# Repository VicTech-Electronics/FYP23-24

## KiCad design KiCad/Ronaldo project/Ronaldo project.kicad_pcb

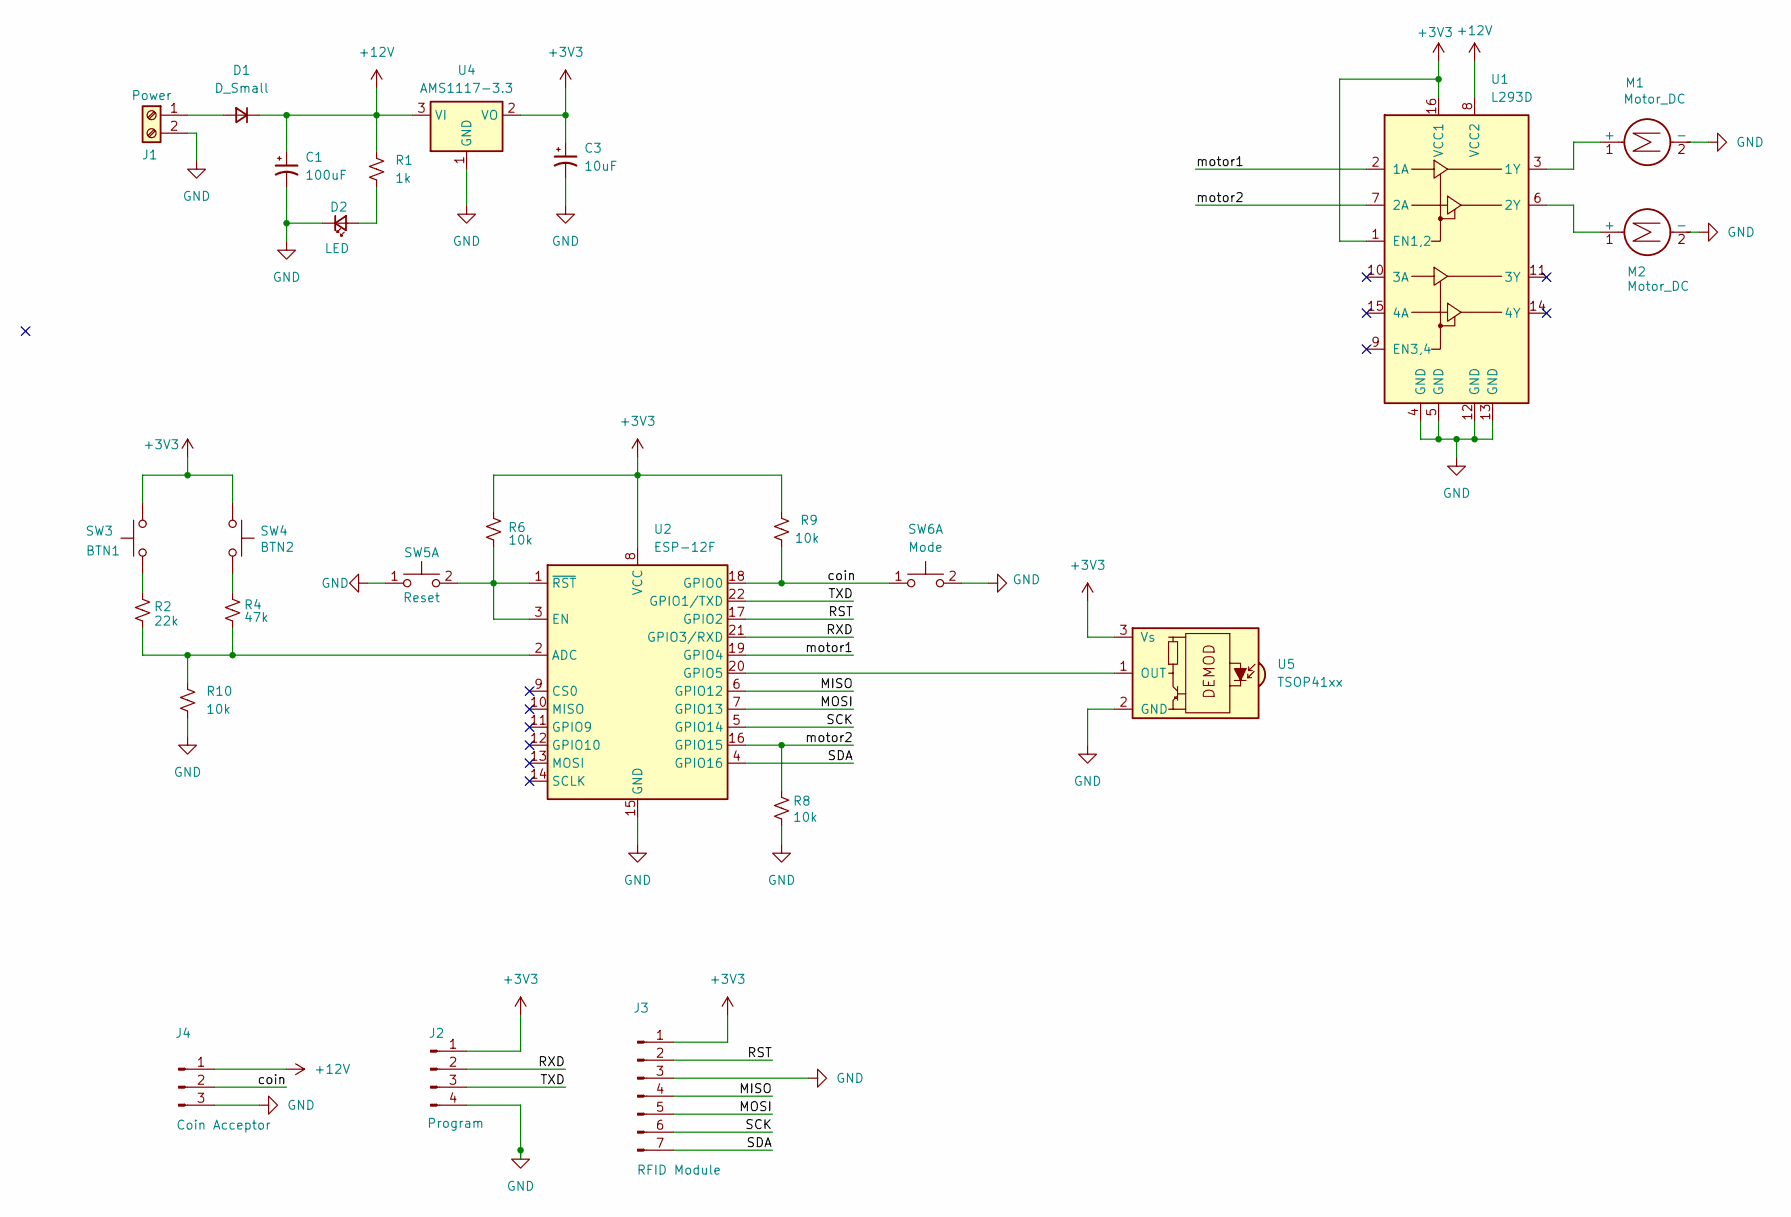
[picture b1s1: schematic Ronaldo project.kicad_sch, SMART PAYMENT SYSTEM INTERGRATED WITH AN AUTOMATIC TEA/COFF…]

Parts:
C1: 100uF; CP_Radial_D5.0mm_P2.50mm
C3: 10uF; CP_Radial_D5.0mm_P2.50mm
D1: D_Small; D_A-405_P10.16mm_Horizontal
D2: LED; LED_D3.0mm
J1: Power; TerminalBlock_bornier-2_P5.08mm
J2: Program; PinHeader_1x04_P2.54mm_Vertical
J3: RFID Module; PinHeader_1x07_P2.54mm_Vertical
J4: Coin Acceptor; PinHeader_1x03_P2.54mm_Vertical
M1, M2: Motor_DC; TerminalBlock_bornier-2_P5.08mm
R1: 1k; R_Axial_DIN0207_L6.3mm_D2.5mm_P10.16mm_Horizontal
R2: 22k; R_Axial_DIN0207_L6.3mm_D2.5mm_P10.16mm_Horizontal
R4: 47k; R_Axial_DIN0207_L6.3mm_D2.5mm_P10.16mm_Horizontal
R6, R8, R9, R10: 10k; R_Axial_DIN0207_L6.3mm_D2.5mm_P10.16mm_Horizontal
SW3: BTN1; TestPoint_2Pads_Pitch2.54mm_Drill0.8mm
SW4: BTN2; TestPoint_2Pads_Pitch2.54mm_Drill0.8mm
SW5: Reset; SW_PUSH_6mm
SW6: Mode; SW_PUSH_6mm
U1: L293D; DIP-16_W7.62mm
U2: ESP-12F; ESP-12E
U4: AMS1117-3.3; SOT-223-3_TabPin2
U5: TSOP41xx; Vishay_MOLD-3Pin

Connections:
+3V3: C3.1, J2.1, J3.1, R6.2, R9.1, SW3.2, SW4.1, U1.1 (EN1,2), U1.16 (VCC1), U2.8 (VCC), U4.2 (VO), U5.3 (Vs)
+12V: C1.1, D1.1 (K), J4.1, R1.1, U1.8 (VCC2), U4.3 (VI)
/MISO: J3.4, U2.6 (GPIO12)
/MOSI: J3.5, U2.7 (GPIO13)
/RST: J3.2, U2.17 (GPIO2)
/RXD: J2.2, U2.21 (GPIO3/RXD)
/SCK: J3.6, U2.5 (GPIO14)
/SDA: J3.7, U2.4 (GPIO16)
/TXD: J2.3, U2.22 (GPIO1/TXD)
/coin: J4.2, R9.2, SW6.1 (C), U2.18 (GPIO0)
/motor1: U1.2 (1A), U2.19 (GPIO4)
/motor2: R8.1, U1.7 (2A), U2.16 (GPIO15)
GND: C1.2, C3.2, D2.1 (K), J1.2, J2.4, J3.3, J4.3, M1.2 (-), M2.2 (-), R8.2, R10.1, SW5.1 (C), SW6.2 (D), U1.4 (GND), U1.5 (GND), U1.12 (GND), U1.13 (GND), U2.15 (GND), U4.1 (GND), U5.2 (GND)
unnamed: D1.2 (A), J1.1
unnamed: D2.2 (A), R1.2
unnamed: M1.1 (+), U1.3 (1Y)
unnamed: M2.1 (+), U1.6 (2Y)
unnamed: R2.2, SW3.1
unnamed: R4.2, SW4.2
unnamed: R6.1, SW5.2 (D), U2.1 (~RST), U2.3 (EN)
unnamed: R2.1, R4.1, R10.2, U2.2 (ADC)
unnamed: U2.20 (GPIO5), U5.1 (OUT)

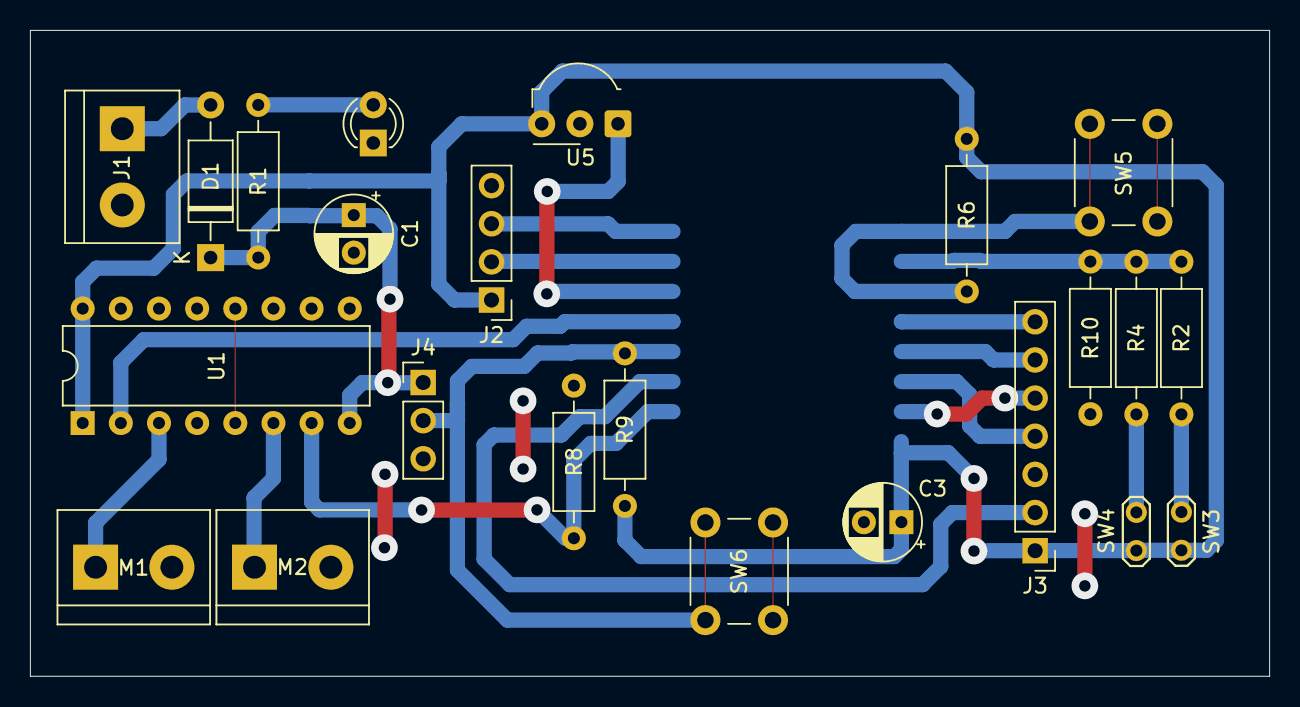
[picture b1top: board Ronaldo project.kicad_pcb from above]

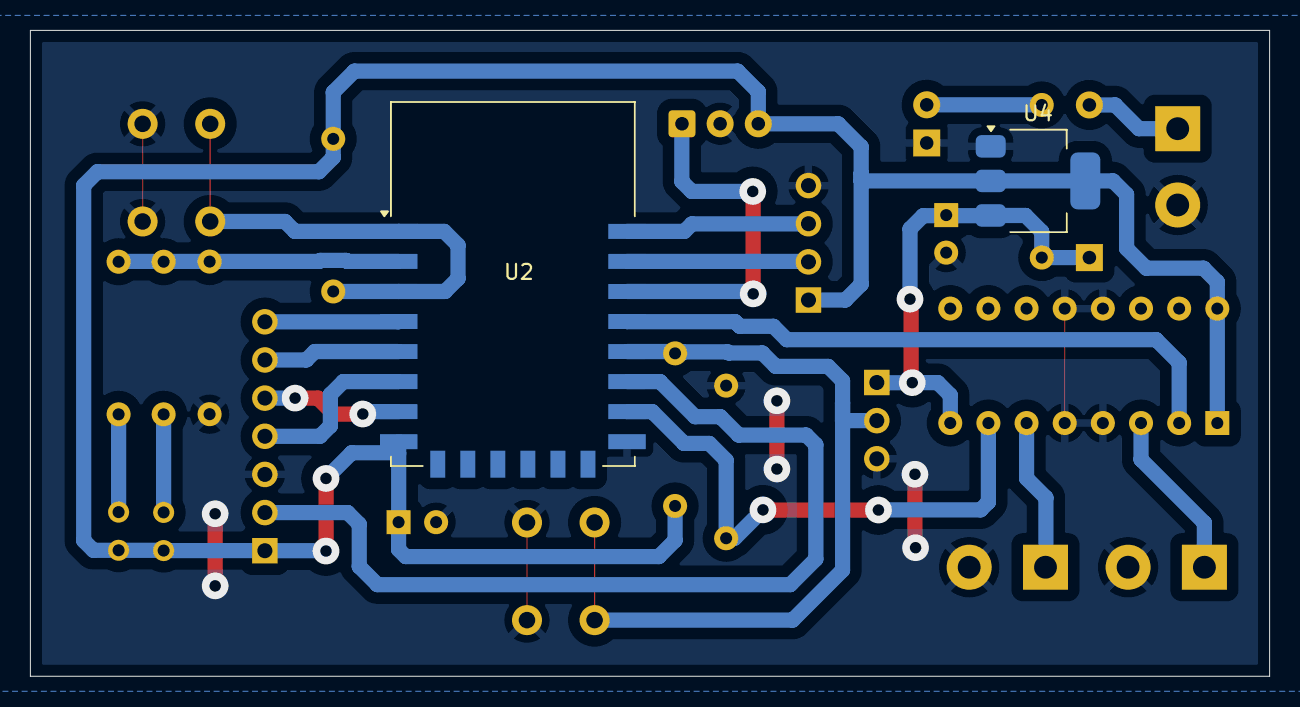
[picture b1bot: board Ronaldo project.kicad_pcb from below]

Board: 2 copper layers, 82.5 x 43.0 mm, 25 parts (2 on the bottom side), 22 nets.

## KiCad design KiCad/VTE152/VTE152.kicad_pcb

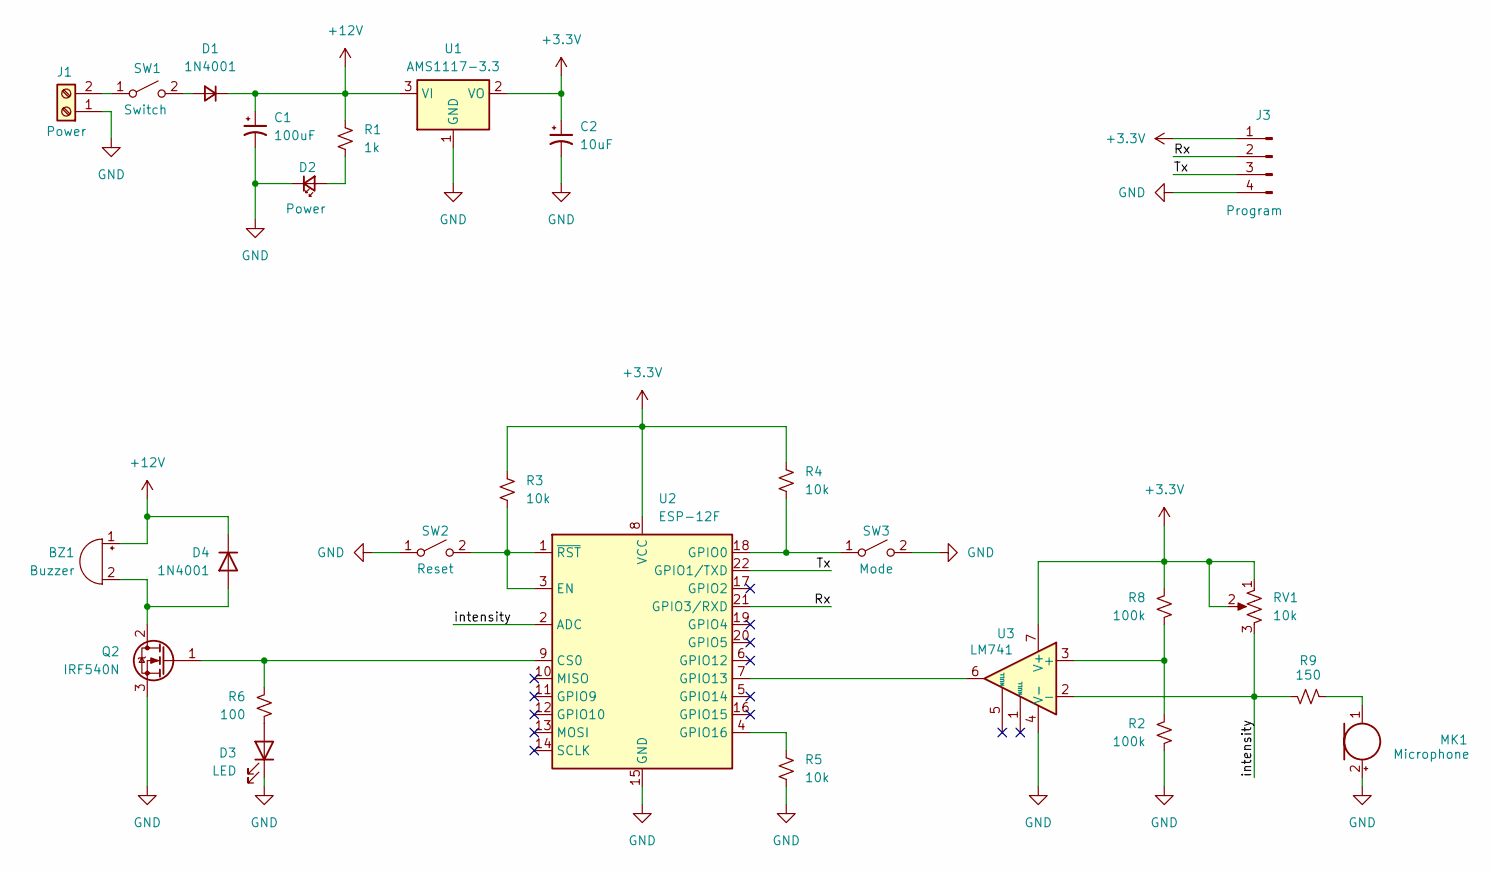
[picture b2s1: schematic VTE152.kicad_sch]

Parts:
BZ1: Buzzer; PinHeader_1x02_P2.54mm_Vertical
C1: 100uF; CP_Radial_D5.0mm_P2.50mm
C2: 10uF; CP_Radial_D5.0mm_P2.50mm
D1: 1N4001; D_A-405_P10.16mm_Horizontal
D2: Power; LED_D3.0mm
D3: LED; LED_D3.0mm
D4: 1N4001; D_DO-41_SOD81_P10.16mm_Horizontal
J1: Power; TerminalBlock_bornier-2_P5.08mm
J3: Program; PinHeader_1x04_P2.54mm_Vertical
MK1: Microphone; MagneticBuzzer_Kobitone_254-EMB73-RO
Q2: IRF540N; TO-220-3_Vertical
R1: 1k; R_Axial_DIN0207_L6.3mm_D2.5mm_P10.16mm_Horizontal
R2, R8: 100k; R_Axial_DIN0207_L6.3mm_D2.5mm_P10.16mm_Horizontal
R3, R4, R5: 10k; R_Axial_DIN0207_L6.3mm_D2.5mm_P10.16mm_Horizontal
R6: 100; R_Axial_DIN0207_L6.3mm_D2.5mm_P10.16mm_Horizontal
R9: 150; R_Axial_DIN0207_L6.3mm_D2.5mm_P10.16mm_Horizontal
RV1: 10k; Potentiometer_Runtron_RM-065_Vertical
SW1: Switch; TestPoint_2Pads_Pitch2.54mm_Drill0.8mm
SW2: Reset; SW_PUSH_6mm
SW3: Mode; SW_PUSH_6mm
U1: AMS1117-3.3; SOT-223-3_TabPin2
U2: ESP-12F; ESP-12E
U3: LM741; DIP-8_W7.62mm_LongPads

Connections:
+3.3V: C2.1, J3.1, R3.1, R4.1, R8.2, RV1.1, RV1.2, U1.2 (VO), U2.8 (VCC), U3.7 (V+)
+12V: BZ1.1 (+), C1.1, D1.1 (K), D4.1 (K), R1.1, U1.3 (VI)
/Rx: J3.2, U2.21 (GPIO3/RXD)
/Tx: J3.3, U2.22 (GPIO1/TXD)
/intensity: R9.1, RV1.3, U2.2 (ADC), U3.2 (-)
GND: C1.2, C2.2, D2.1 (K), D3.1 (K), J1.1, J3.4, MK1.2 (+), Q2.3 (S), R2.1, R5.2, SW2.1 (A), SW3.2 (B), U1.1 (GND), U2.15 (GND), U3.4 (V-)
unnamed: BZ1.2 (-), D4.2 (A), Q2.2 (D)
unnamed: D1.2 (A), SW1.2 (B)
unnamed: D2.2 (A), R1.2
unnamed: D3.2 (A), R6.2
unnamed: J1.2, SW1.1 (A)
unnamed: MK1.1 (-), R9.2
unnamed: Q2.1 (G), R6.1, U2.9 (CS0)
unnamed: R3.2, SW2.2 (B), U2.1 (~RST), U2.3 (EN)
unnamed: R4.2, SW3.1 (A), U2.18 (GPIO0)
unnamed: U2.7 (GPIO13), U3.6
unnamed: R5.1, U2.4 (GPIO16)
unnamed: R2.2, R8.1, U3.3 (+)

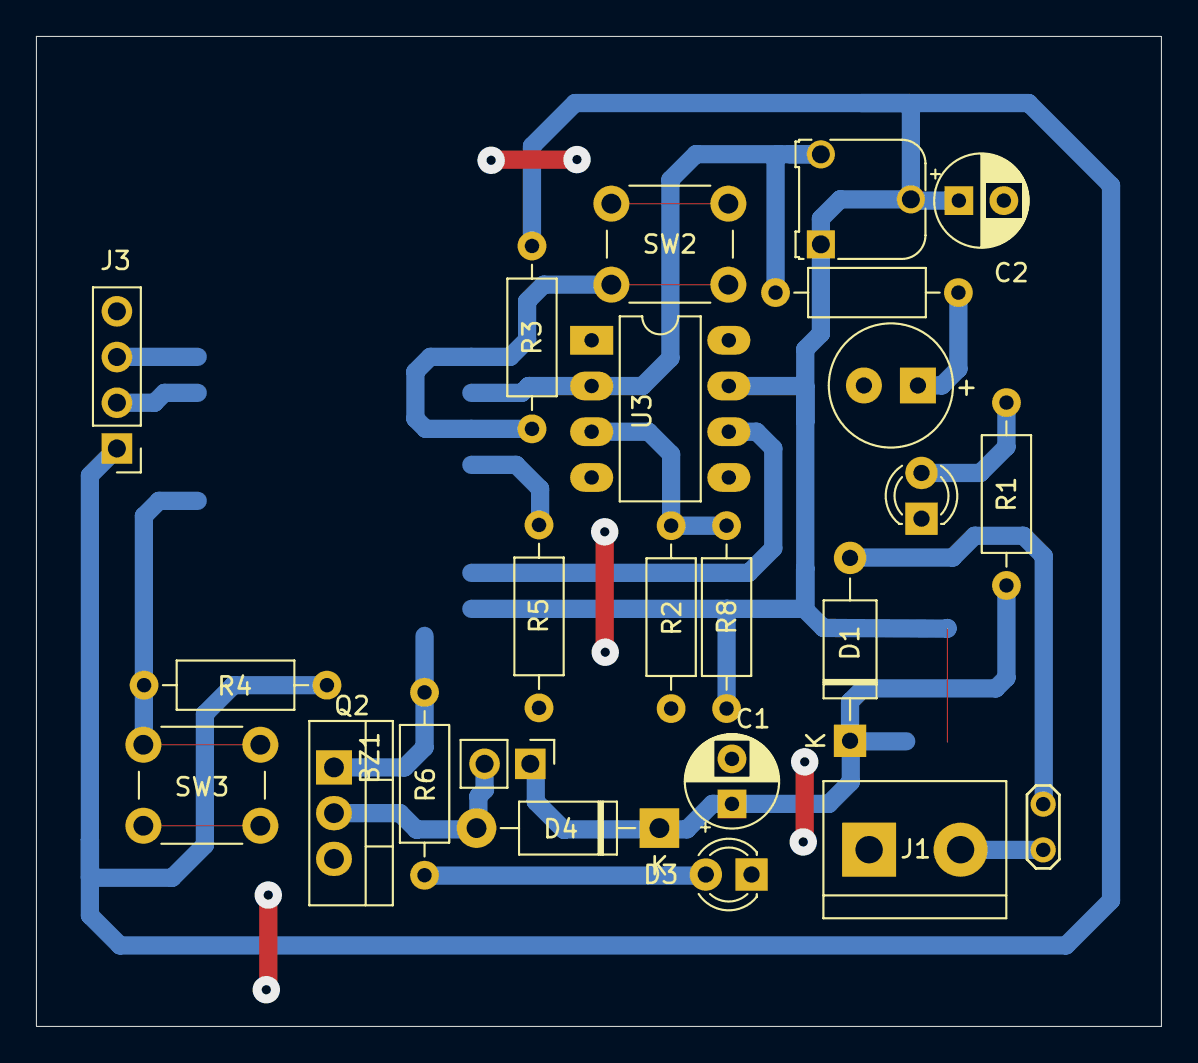
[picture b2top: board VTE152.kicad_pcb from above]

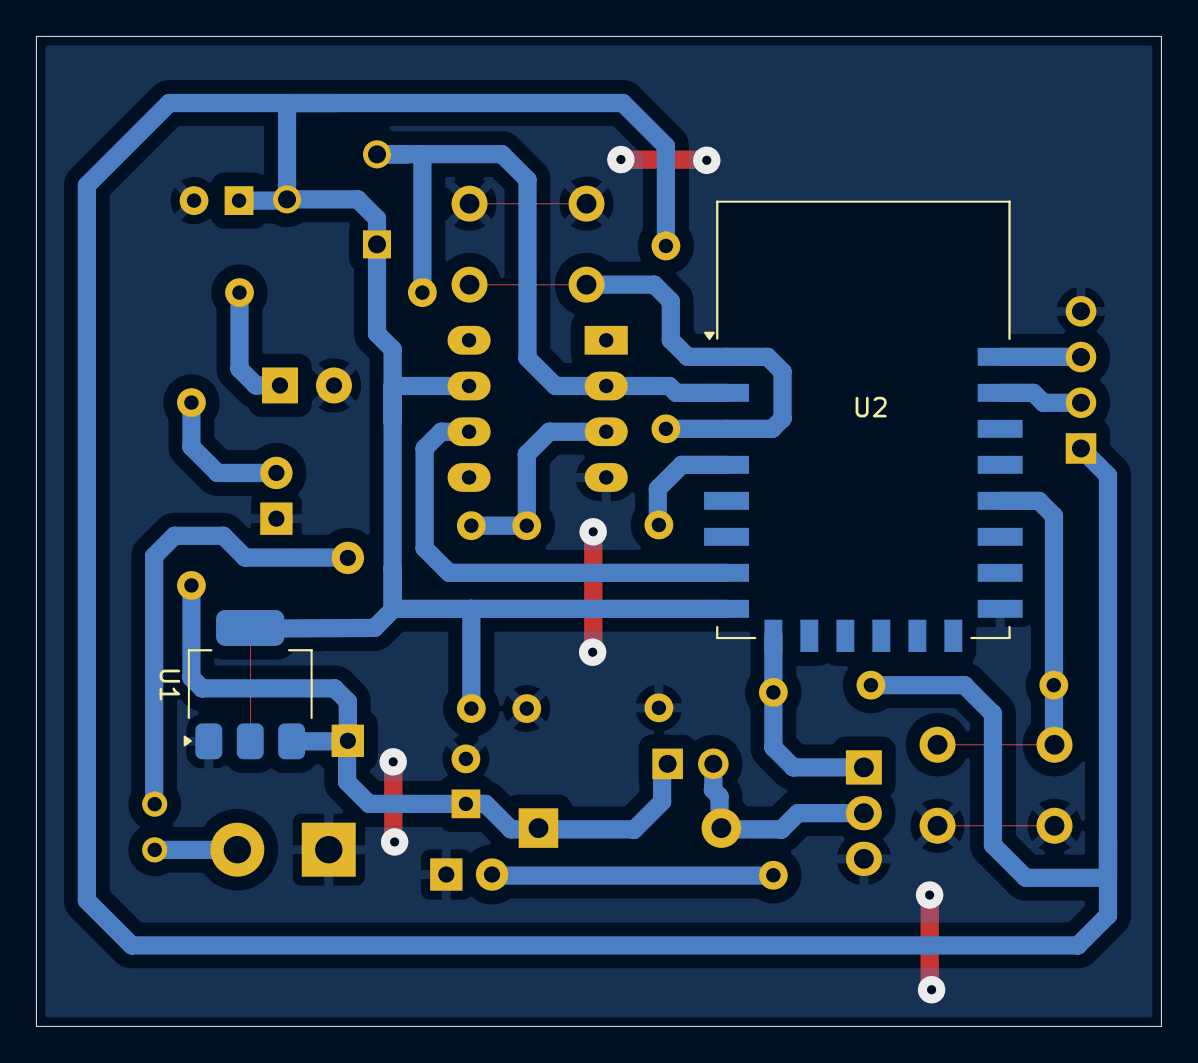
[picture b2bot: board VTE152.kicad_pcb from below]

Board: 2 copper layers, 62.5 x 55.0 mm, 26 parts (2 on the bottom side), 18 nets.

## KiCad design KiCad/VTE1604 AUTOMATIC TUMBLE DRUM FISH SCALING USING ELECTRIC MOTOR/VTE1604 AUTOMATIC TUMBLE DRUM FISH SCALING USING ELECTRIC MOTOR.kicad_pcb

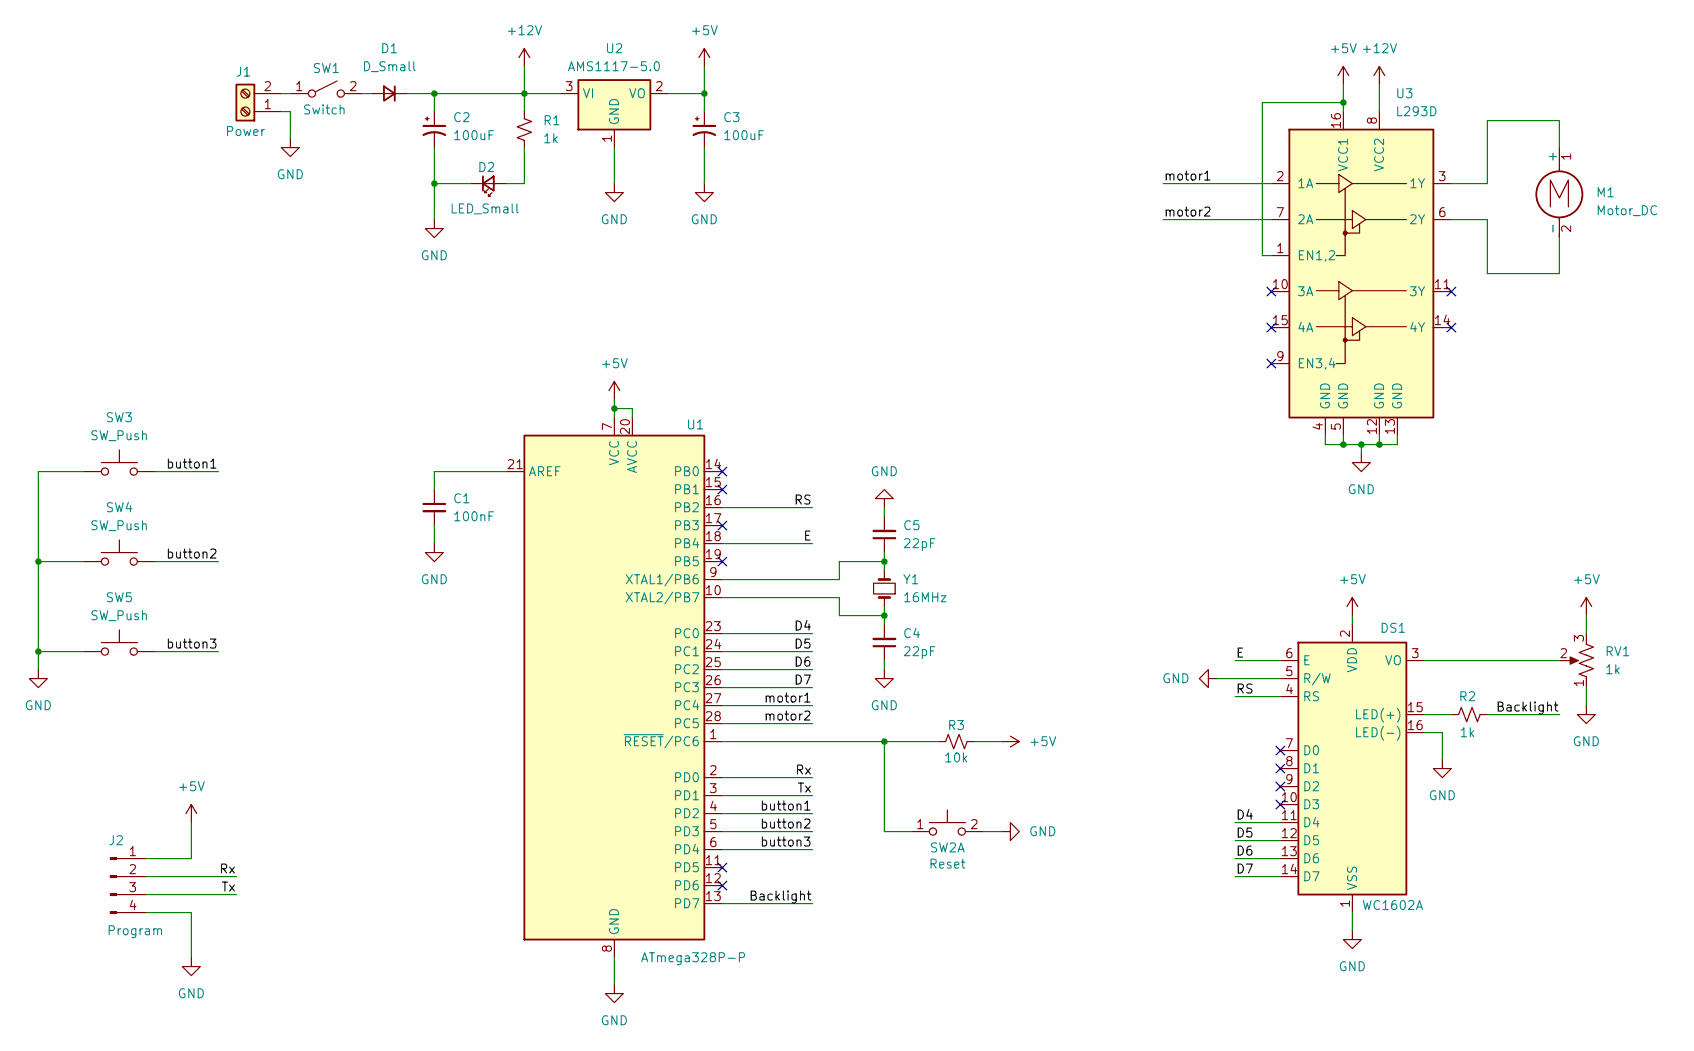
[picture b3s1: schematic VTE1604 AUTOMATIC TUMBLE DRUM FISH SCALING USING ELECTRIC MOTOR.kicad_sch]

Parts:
C1: 100nF; C_Disc_D3.0mm_W1.6mm_P2.50mm
C2, C3: 100uF; CP_Radial_D5.0mm_P2.50mm
C4, C5: 22pF; C_Disc_D3.0mm_W1.6mm_P2.50mm
D1: D_Small; D_A-405_P10.16mm_Horizontal
D2: LED_Small; LED_D3.0mm
DS1: WC1602A
J1: Power; TerminalBlock_bornier-2_P5.08mm
J2: Program; PinHeader_1x04_P2.54mm_Vertical
M1: Motor_DC; TerminalBlock_bornier-2_P5.08mm
R1, R2: 1k; R_Axial_DIN0207_L6.3mm_D2.5mm_P10.16mm_Horizontal
R3: 10k; R_Axial_DIN0207_L6.3mm_D2.5mm_P10.16mm_Horizontal
RV1: 1k; Potentiometer_Runtron_RM-065_Vertical
SW1: Switch; TestPoint_2Pads_Pitch2.54mm_Drill0.8mm
SW2: Reset; SW_PUSH_6mm
SW3, SW4, SW5: SW_Push; TestPoint_2Pads_Pitch2.54mm_Drill0.8mm
U1: ATmega328P-P; DIP-28_W7.62mm_Socket_LongPads
U2: AMS1117-5.0; SOT-223-3_TabPin2
U3: L293D; DIP-16_W7.62mm_Socket_LongPads
Y1: 16MHz; Crystal_HC50_Vertical

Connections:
+5V: C3.1, DS1.2 (VDD), J2.1, R3.2, RV1.3, U1.7 (VCC), U1.20 (AVCC), U2.2 (VO), U3.1 (EN1,2), U3.16 (VCC1)
+12V: C2.1, D1.1 (K), R1.1, U2.3 (VI), U3.8 (VCC2)
/Backlight: R2.2, U1.13 (PD7)
/D4: DS1.11 (D4), U1.23 (PC0)
/D5: DS1.12 (D5), U1.24 (PC1)
/D6: DS1.13 (D6), U1.25 (PC2)
/D7: DS1.14 (D7), U1.26 (PC3)
/E: DS1.6 (E), U1.18 (PB4)
/RS: DS1.4 (RS), U1.16 (PB2)
/Rx: J2.2, U1.2 (PD0)
/Tx: J2.3, U1.3 (PD1)
/button1: SW3.2, U1.4 (PD2)
/button2: SW4.2, U1.5 (PD3)
/button3: SW5.2, U1.6 (PD4)
/motor1: U1.27 (PC4), U3.2 (1A)
/motor2: U1.28 (PC5), U3.7 (2A)
GND: C1.2, C2.2, C3.2, C4.1, C5.2, D2.1 (K), DS1.1 (VSS), DS1.5 (R/W), DS1.16 (LED(-)), J1.1, J2.4, RV1.1, SW2.2 (D), SW3.1, SW4.1, SW5.1, U1.8 (GND), U1.22 (GND), U2.1 (GND), U3.4 (GND), U3.5 (GND), U3.12 (GND), U3.13 (GND)
unnamed: D1.2 (A), SW1.2 (B)
unnamed: D2.2 (A), R1.2
unnamed: DS1.15 (LED(+)), R2.1
unnamed: DS1.3 (VO), RV1.2
unnamed: J1.2, SW1.1 (A)
unnamed: M1.1 (+), U3.3 (1Y)
unnamed: M1.2 (-), U3.6 (2Y)
unnamed: R3.1, SW2.1 (C), U1.1 (~RESET/PC6)
unnamed: C1.1, U1.21 (AREF)
unnamed: C5.1, U1.9 (XTAL1/PB6), Y1.2
unnamed: C4.2, U1.10 (XTAL2/PB7), Y1.1

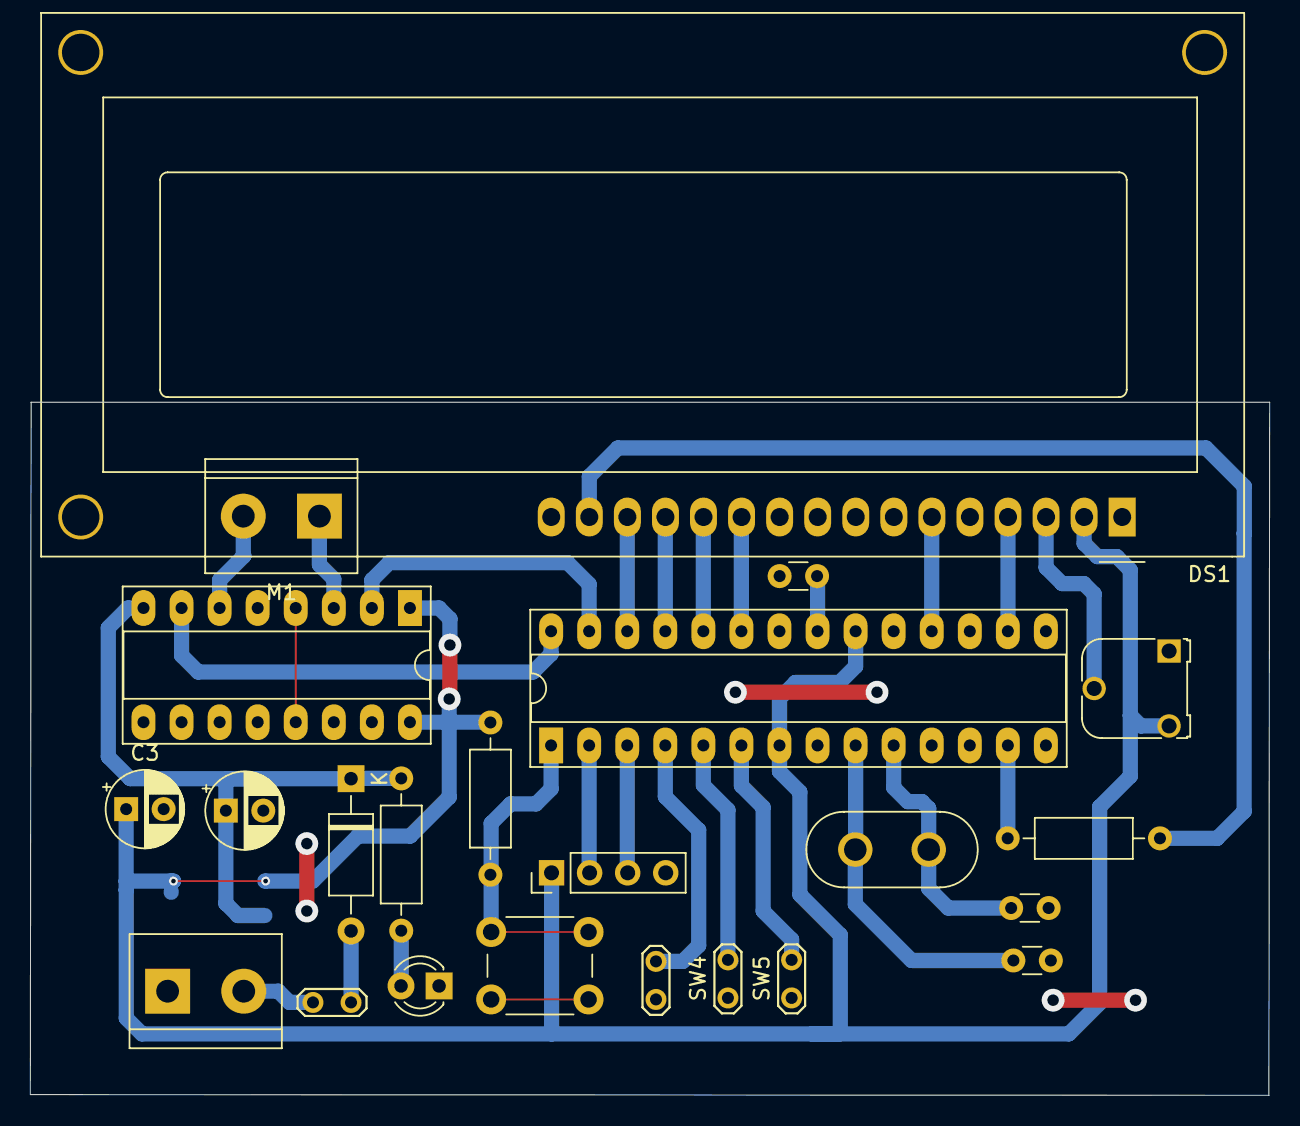
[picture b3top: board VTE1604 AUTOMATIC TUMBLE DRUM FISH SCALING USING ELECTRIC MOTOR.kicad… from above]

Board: 2 copper layers, 82.7 x 46.2 mm, 24 parts (1 on the bottom side), 28 nets.

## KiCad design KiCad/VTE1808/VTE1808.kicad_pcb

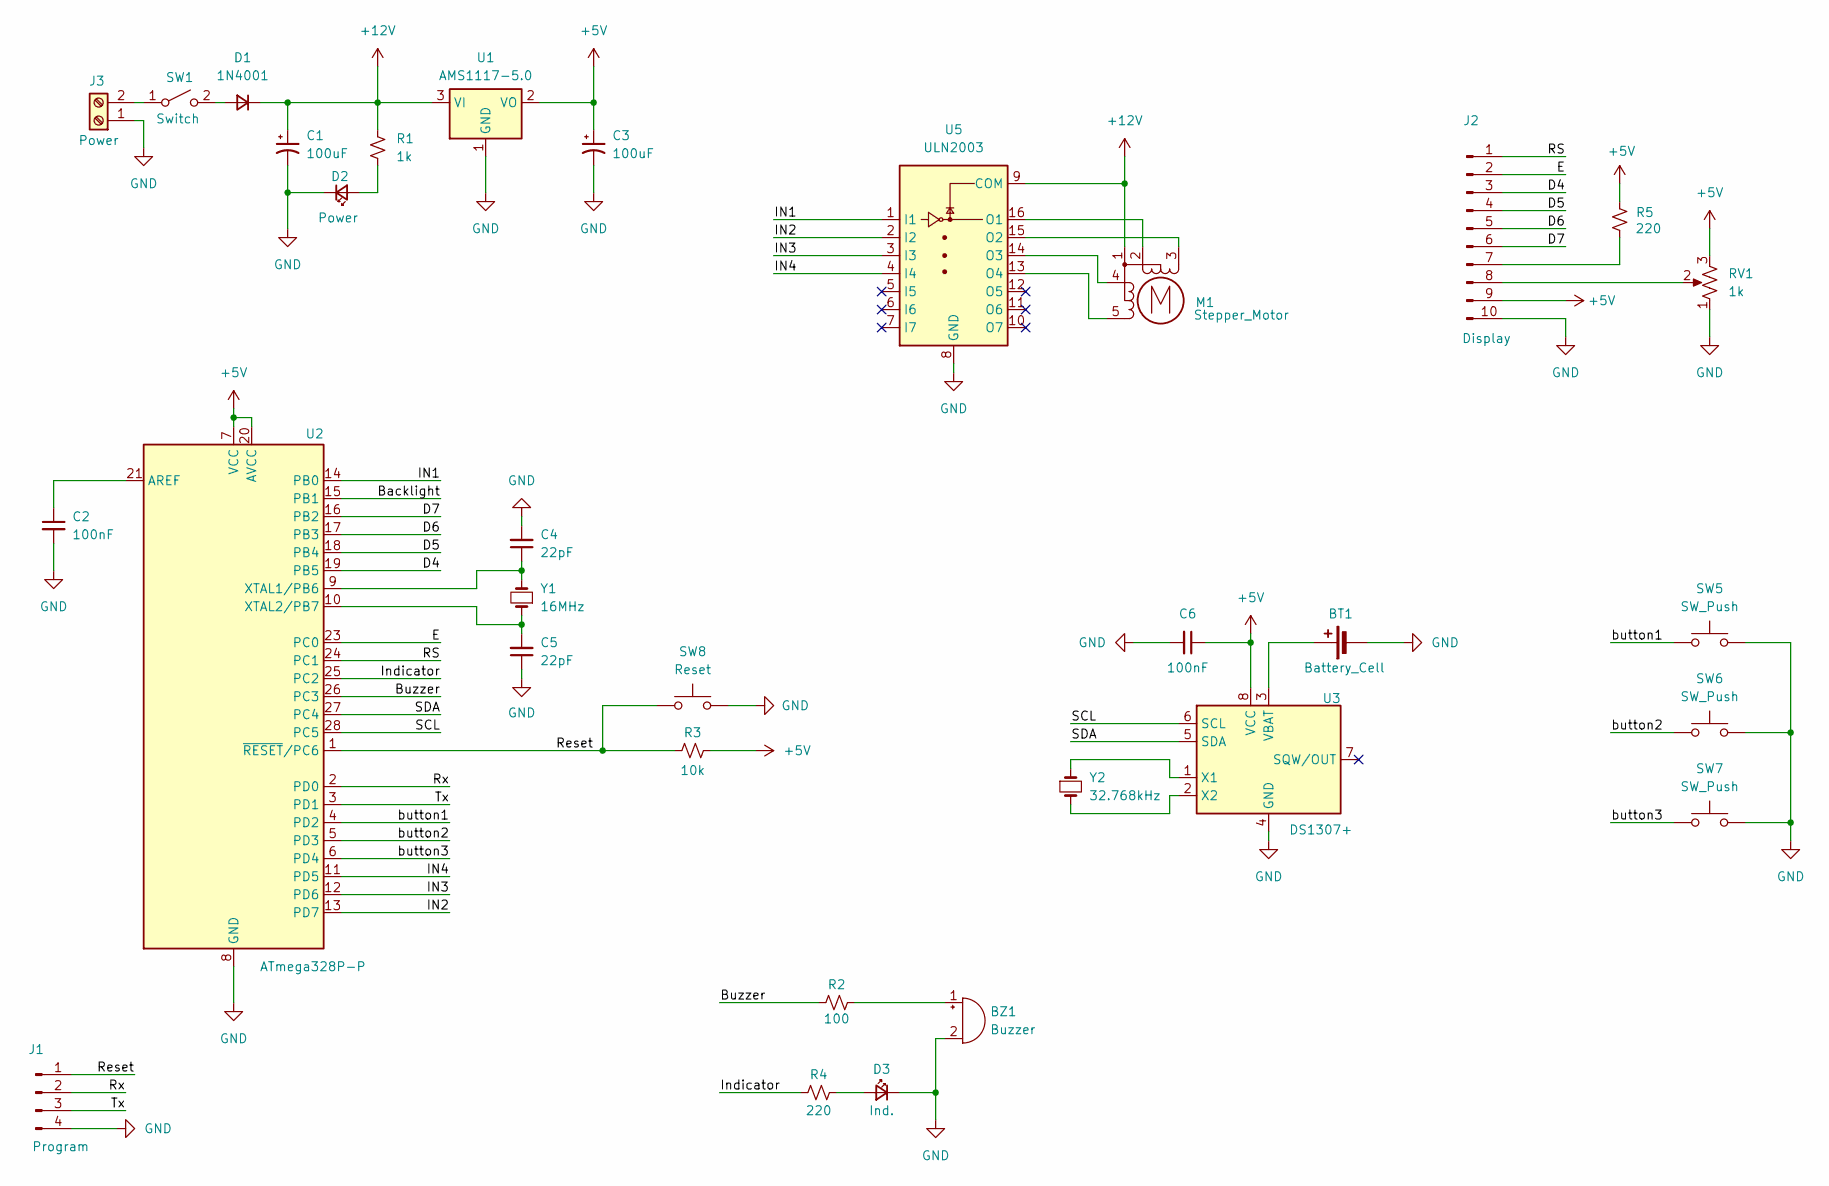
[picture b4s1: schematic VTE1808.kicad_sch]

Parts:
BT1: Battery_Cell; BatteryHolder_Keystone_1058_1x2032
BZ1: Buzzer; Buzzer_12x9.5RM7.6
C1, C3: 100uF; CP_Radial_D5.0mm_P2.50mm
C2, C6: 100nF; C_Disc_D3.0mm_W1.6mm_P2.50mm
C4, C5: 22pF; C_Disc_D3.0mm_W1.6mm_P2.50mm
D1: 1N4001; D_A-405_P10.16mm_Horizontal
D2: Power; LED_D3.0mm
D3: Ind.; LED_D3.0mm
J1: Program; PinHeader_1x04_P2.54mm_Vertical
J2: Display; PinHeader_1x10_P2.54mm_Vertical
J3: Power; TerminalBlock_bornier-2_P5.08mm
M1: Stepper_Motor; PinHeader_1x05_P2.54mm_Vertical
R1: 1k; R_Axial_DIN0207_L6.3mm_D2.5mm_P10.16mm_Horizontal
R2: 100; R_Axial_DIN0207_L6.3mm_D2.5mm_P10.16mm_Horizontal
R3: 10k; R_Axial_DIN0207_L6.3mm_D2.5mm_P10.16mm_Horizontal
R4, R5: 220; R_Axial_DIN0207_L6.3mm_D2.5mm_P10.16mm_Horizontal
RV1: 1k; Potentiometer_Runtron_RM-065_Vertical
SW1: Switch; TestPoint_2Pads_Pitch2.54mm_Drill0.8mm
SW5, SW6, SW7: SW_Push; TestPoint_2Pads_Pitch2.54mm_Drill0.8mm
SW8: Reset; SW_PUSH_6mm
U1: AMS1117-5.0; SOT-223-3_TabPin2
U2: ATmega328P-P; DIP-28_W7.62mm_Socket_LongPads
U3: DS1307+; DIP-8_W7.62mm
U5: ULN2003; DIP-16_W7.62mm_LongPads
Y1: 16MHz; Crystal_HC50_Vertical
Y2: 32.768kHz; Crystal_C26-LF_D2.1mm_L6.5mm_Horizontal

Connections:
+5V: C3.1, C6.1, J2.9, R3.2, R5.2, RV1.3, U1.2 (VO), U2.7 (VCC), U2.20 (AVCC), U3.8 (VCC)
+12V: C1.1, D1.1 (K), M1.1, R1.1, U1.3 (VI), U5.9 (COM)
/Backlight: U2.15 (PB1)
/Buzzer: R2.1, U2.26 (PC3)
/D4: J2.3, U2.19 (PB5)
/D5: J2.4, U2.18 (PB4)
/D6: J2.5, U2.17 (PB3)
/D7: J2.6, U2.16 (PB2)
/E: J2.2, U2.23 (PC0)
/IN1: U2.14 (PB0), U5.1 (I1)
/IN2: U2.13 (PD7), U5.2 (I2)
/IN3: U2.12 (PD6), U5.3 (I3)
/IN4: U2.11 (PD5), U5.4 (I4)
/Indicator: R4.1, U2.25 (PC2)
/RS: J2.1, U2.24 (PC1)
/Reset: J1.1, R3.1, SW8.1, U2.1 (~RESET/PC6)
/Rx: J1.2, U2.2 (PD0)
/SCL: U2.28 (PC5), U3.6 (SCL)
/SDA: U2.27 (PC4), U3.5 (SDA)
/Tx: J1.3, U2.3 (PD1)
/button1: SW5.2, U2.4 (PD2)
/button2: SW6.2, U2.5 (PD3)
/button3: SW7.2, U2.6 (PD4)
GND: BT1.2 (-), BZ1.2 (-), C1.2, C2.2, C3.2, C4.2, C5.1, C6.2, D2.1 (K), D3.1 (K), J1.4, J2.10, J3.1, RV1.1, SW5.1, SW6.1, SW7.1, SW8.2, U1.1 (GND), U2.8 (GND), U2.22 (GND), U3.4 (GND), U5.8 (GND)
unnamed: BT1.1 (+), U3.3 (VBAT)
unnamed: BZ1.1 (+), R2.2
unnamed: D1.2 (A), SW1.2 (B)
unnamed: D2.2 (A), R1.2
unnamed: D3.2 (A), R4.2
unnamed: J2.7, R5.1
unnamed: J2.8, RV1.2
unnamed: J3.2, SW1.1 (A)
unnamed: M1.3 (-), U5.15 (O2)
unnamed: C2.1, U2.21 (AREF)
unnamed: C4.1, U2.9 (XTAL1/PB6), Y1.2
unnamed: C5.2, U2.10 (XTAL2/PB7), Y1.1
unnamed: U3.1 (X1), Y2.1
unnamed: U3.2 (X2), Y2.2
unnamed: M1.2, U5.16 (O1)
unnamed: M1.4, U5.14 (O3)
unnamed: M1.5, U5.13 (O4)

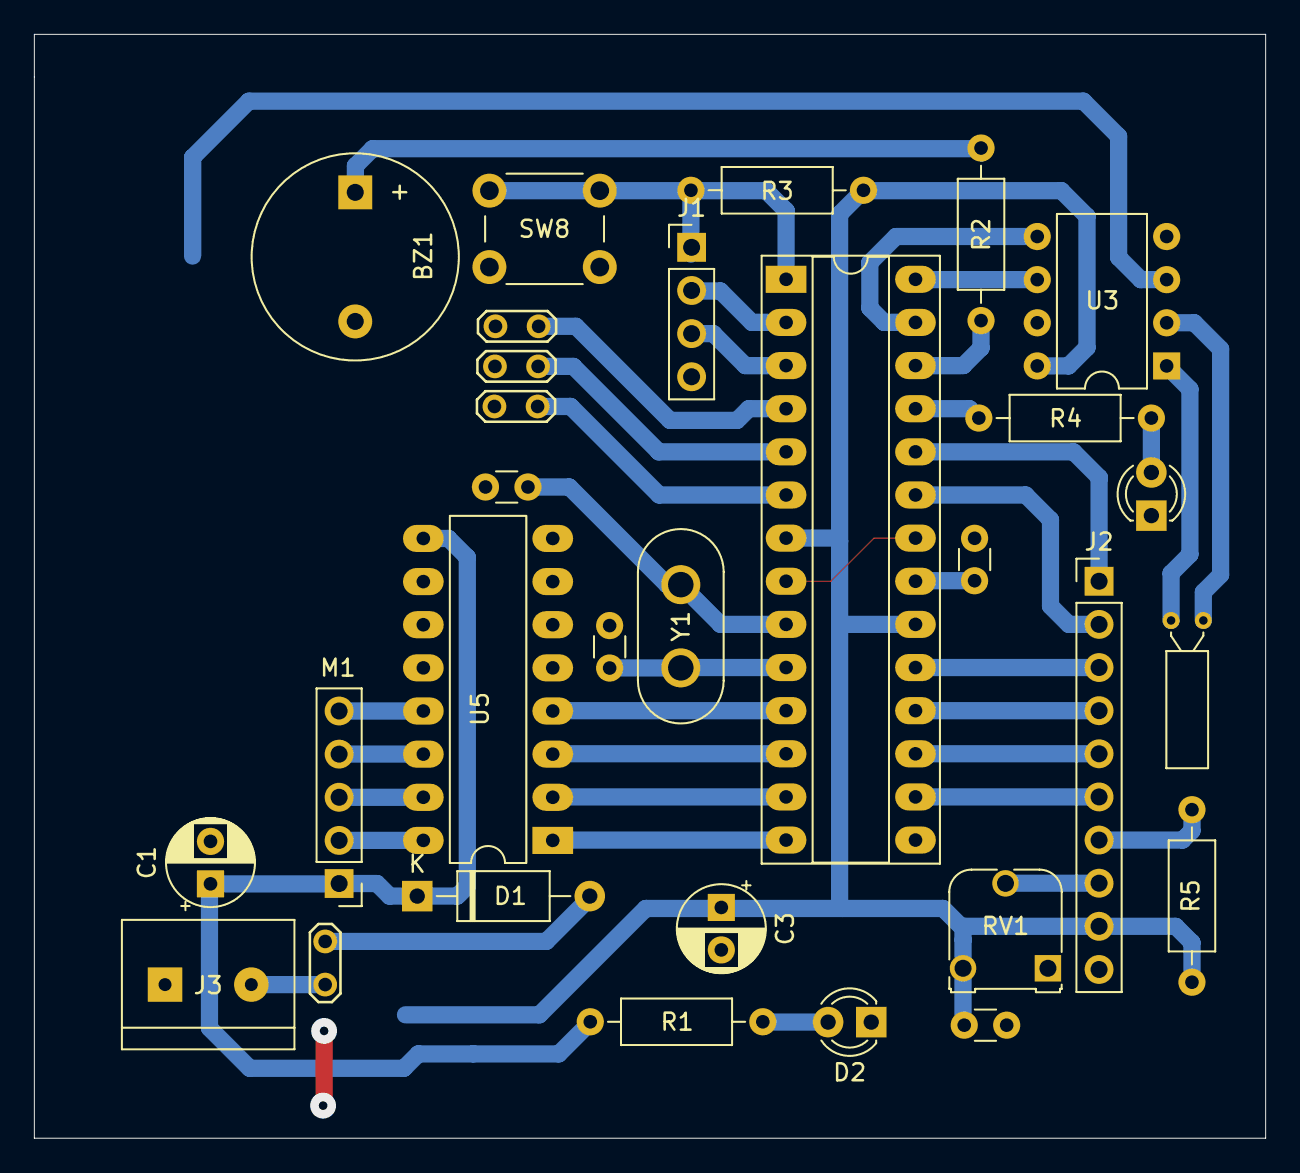
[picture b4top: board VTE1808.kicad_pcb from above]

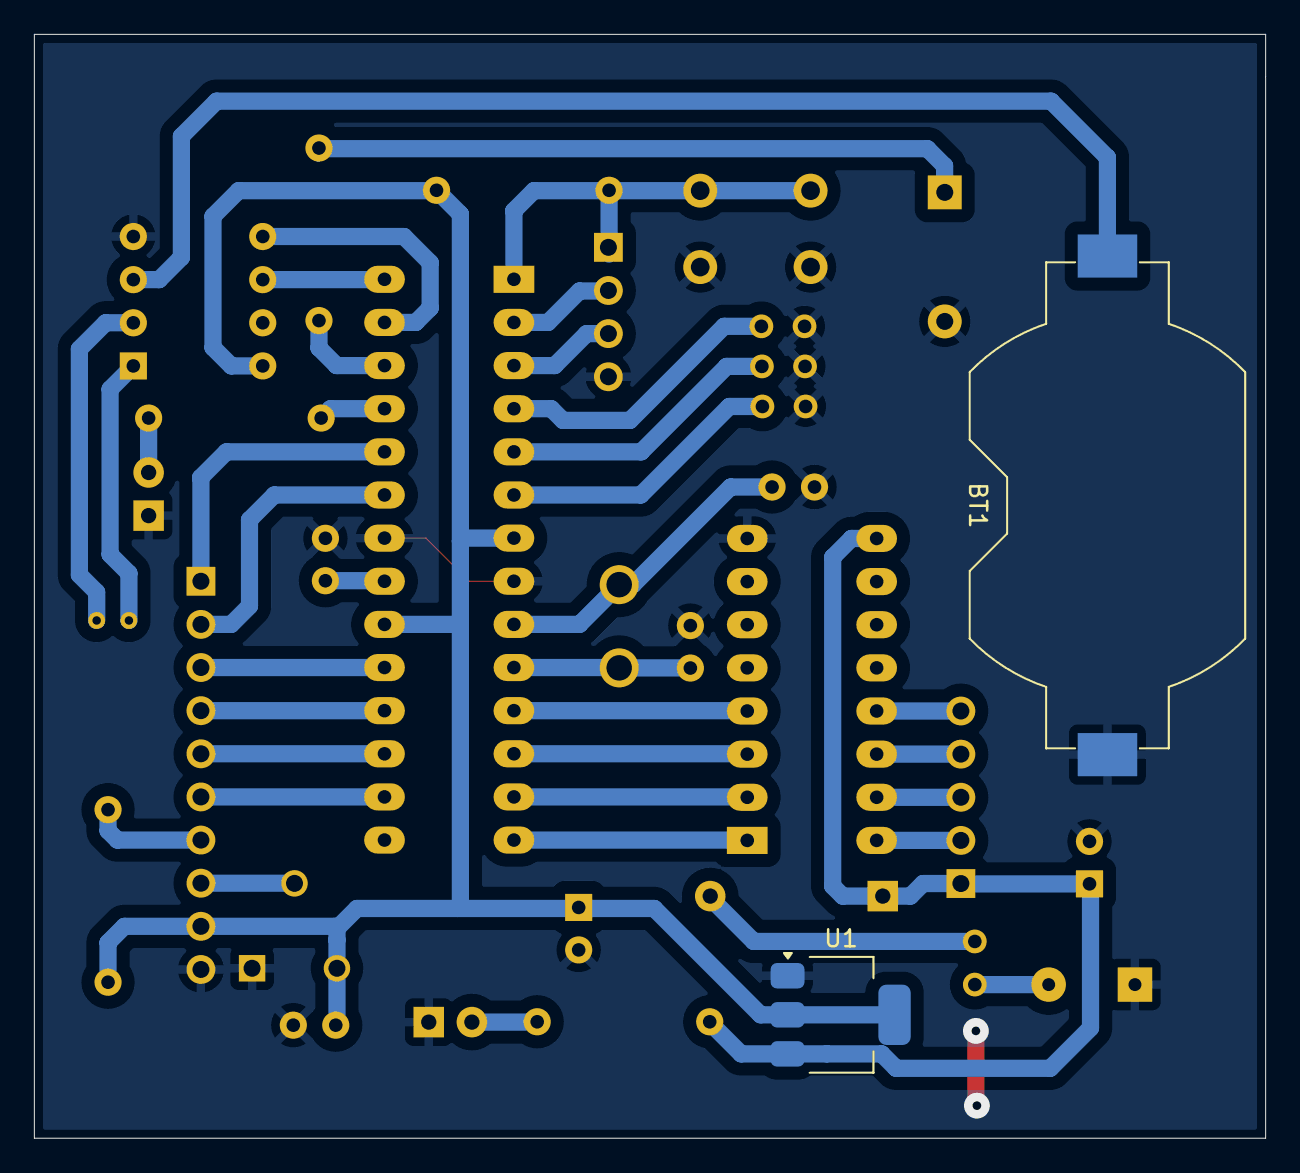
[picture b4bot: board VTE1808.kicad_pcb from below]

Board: 2 copper layers, 72.5 x 65.0 mm, 32 parts (2 on the bottom side), 40 nets.
